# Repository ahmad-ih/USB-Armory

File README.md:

View this project on [CADLAB.io](https://cadlab.io/project/22758). 

# USB-Armory

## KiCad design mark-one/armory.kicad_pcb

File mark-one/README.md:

Introduction
============

USB armory | https://inversepath.com/usbarmory  
Copyright (c) F-Secure Corporation

The USB armory from [Inverse Path](https://inversepath.com) is an open source
hardware design, implementing a flash drive sized computer.

This repository is aimed towards developers, if you wish to purchase a USB
armory board please see the [ordering information](https://inversepath.com/usbarmory#ordering).

Revision information
====================

This directory contains the hardware design for the USB armory board, first
revision (Mark I).

Current schematics and layout files have been designed in KiCad (`release
2014-01-25 - 0.201403191418+4754~10~ubuntu12.04.1`)

PCB information
===============

6 layers, 2.00mm thickness  
Outer layers 0.5 oz base copper foil  
Inner layers   1 oz base copper foil  
width (X) 65.6 mm, height (Y) 19.5 mm  
Electroless Nickel Immersion Gold (ENIG) surface finish  
Selective hard gold (min 0.75um) plating for J2 (USB)  
Black resist, white component legend

Layers
------

Order and type of copper layers:  
  TOP:         signal, front components  
  SIGNAL 1:    signal  
  GND POWER 1: ground and power plane  
  GND POWER 2: ground and power plane  
  SIGNAL 2:    signal  
  BOTTOM:      signal, back components  

| Layer | Description               |  Thickness (in um)  |
|:-----:|---------------------------|:-------------------:|
|       | LPI mask                  |   15                |
|       | ENIG plating              |   18                |
|   1   | copper                    |   17                |
|       | prepreg, 3 x PP 1080      |  240 -> 220         |
|   2   | copper                    |   35                |
|       | core, FR4  35/35          |  300                |
|   3   | copper                    |   35                |
|       | prepreg, 4 x PP 7628      |  760 -> 720         |
|   4   | copper                    |   35                |
|       | core, FR4  35/35          |  300                |
|   5   | copper                    |   35                |
|       | prepreg, 3 x PP 1080      |  240 -> 220         |
|   6   | copper                    |   17                |
|       | ENIG plating              |   18                |
|       | LPI mask                  |   15                |

Material: Isola PCL370-HR
Total thickness: 2.0 mm

DRC information
---------------

Minimum track width:            0.127 mm  
Minimum via diameter:           0.406 mm  
Outer layer track width:        0.127 mm  
Outer layer isolation distance: 0.127 mm  
Outer layer annular ring:       0.075 mm  
Inner layer track width:        0.127 mm  
Inner layer isolation distance: 0.127 mm  
Inner layer annular ring:       0.075 mm  
Smallest final hole (plated):   0.150 mm

Regulatory compliance & handling
================================

The USB armory board is intended for use as a development platform for hardware
or software. The board is an open system design, which does not include a
shielded enclosure. This may cause interference to other electrical or
electronic devices in close proximity. In a domestic environment, this product
may cause radio interference in which case the user may be required to take
adequate measures. In addition, this board should not be used near any medical
equipment or RF devices.

The board is sensitive to ESD. Hold the board only by its edges. After removing
the board from its box, place it on a grounded, static-free surface.

The board can become hot, like any fan-less design, during continuous high CPU
loads, mind its temperature while handling it.

License
=======

USB armory | https://inversepath.com/usbarmory  
Copyright (c) F-Secure Corporation

This is an open hardware design licensed under the terms of the CERN Open
Hardware Licence (OHL) v1.2.

You may redistribute and modify this documentation under the terms of the CERN
OHL v.1.2 (http://ohwr.org/cernohl). This documentation is distributed WITHOUT
ANY EXPRESS OR IMPLIED WARRANTY, INCLUDING OF MERCHANTABILITY, SATISFACTORY
QUALITY AND FITNESS FOR A PARTICULAR PURPOSE. Please see the CERN OHL v.1.2 for
applicable conditions.

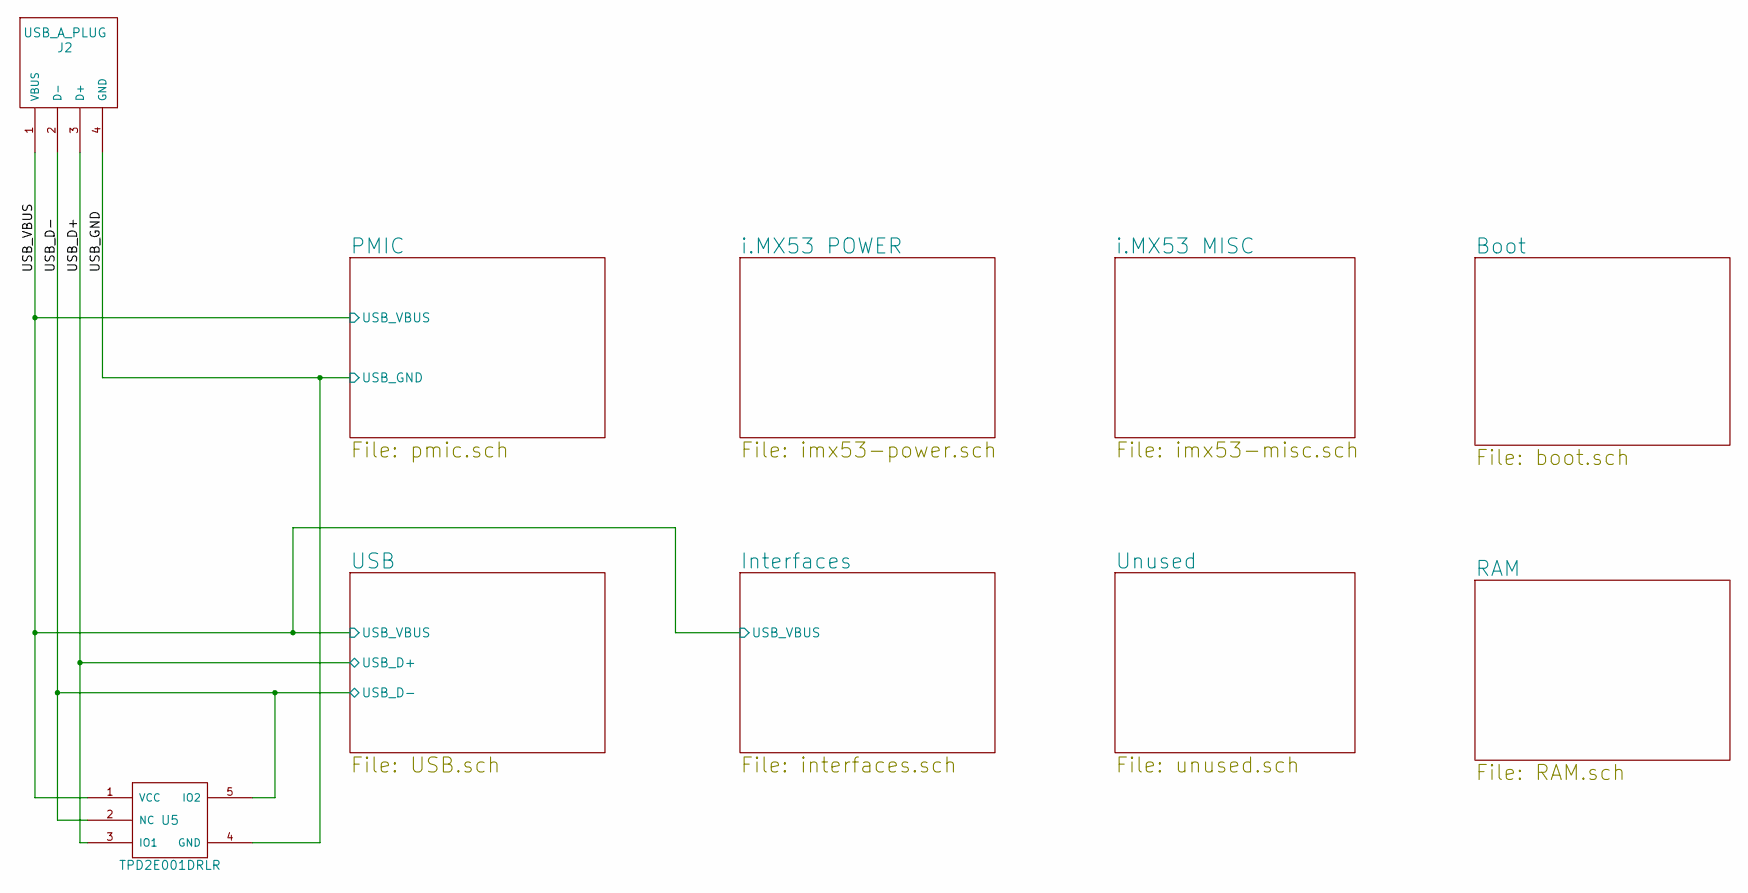
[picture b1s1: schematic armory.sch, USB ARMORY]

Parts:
J2: USB_A_PLUG; usb-PCB
U5: TPD2E001DRLR; R-PDSO-N5; Mfg PN TPD2E001DRLR

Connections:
/Interfaces/USB_VBUS: J2.1 (VBUS), U5.1 (VCC); also elsewhere on the board
/USB/USB_D+: J2.3 (D+), U5.3 (IO1); also elsewhere on the board
/USB/USB_D-: J2.2 (D-), U5.2 (NC), U5.5 (IO2); also elsewhere on the board
GND: J2.4 (GND), U5.4 (GND); also elsewhere on the board

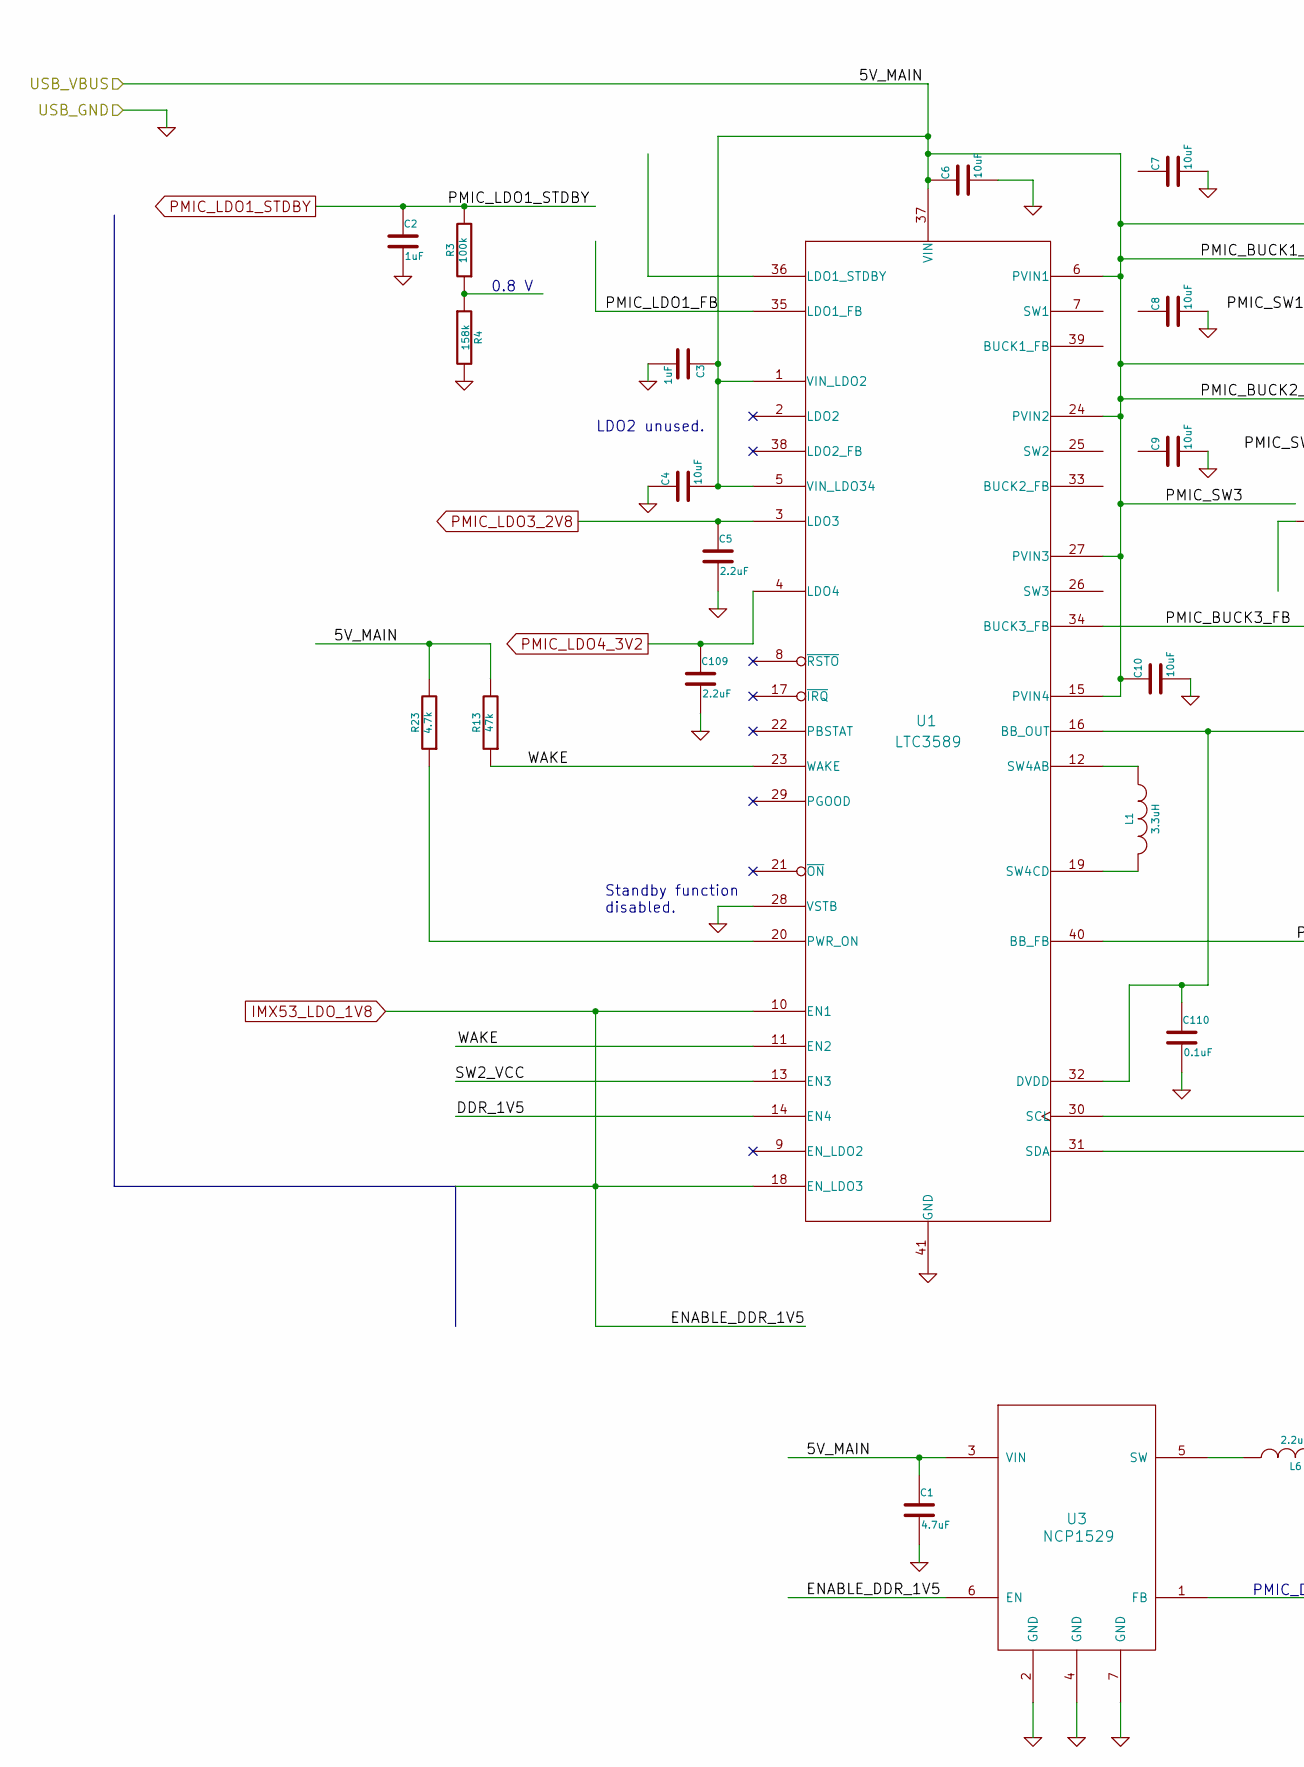
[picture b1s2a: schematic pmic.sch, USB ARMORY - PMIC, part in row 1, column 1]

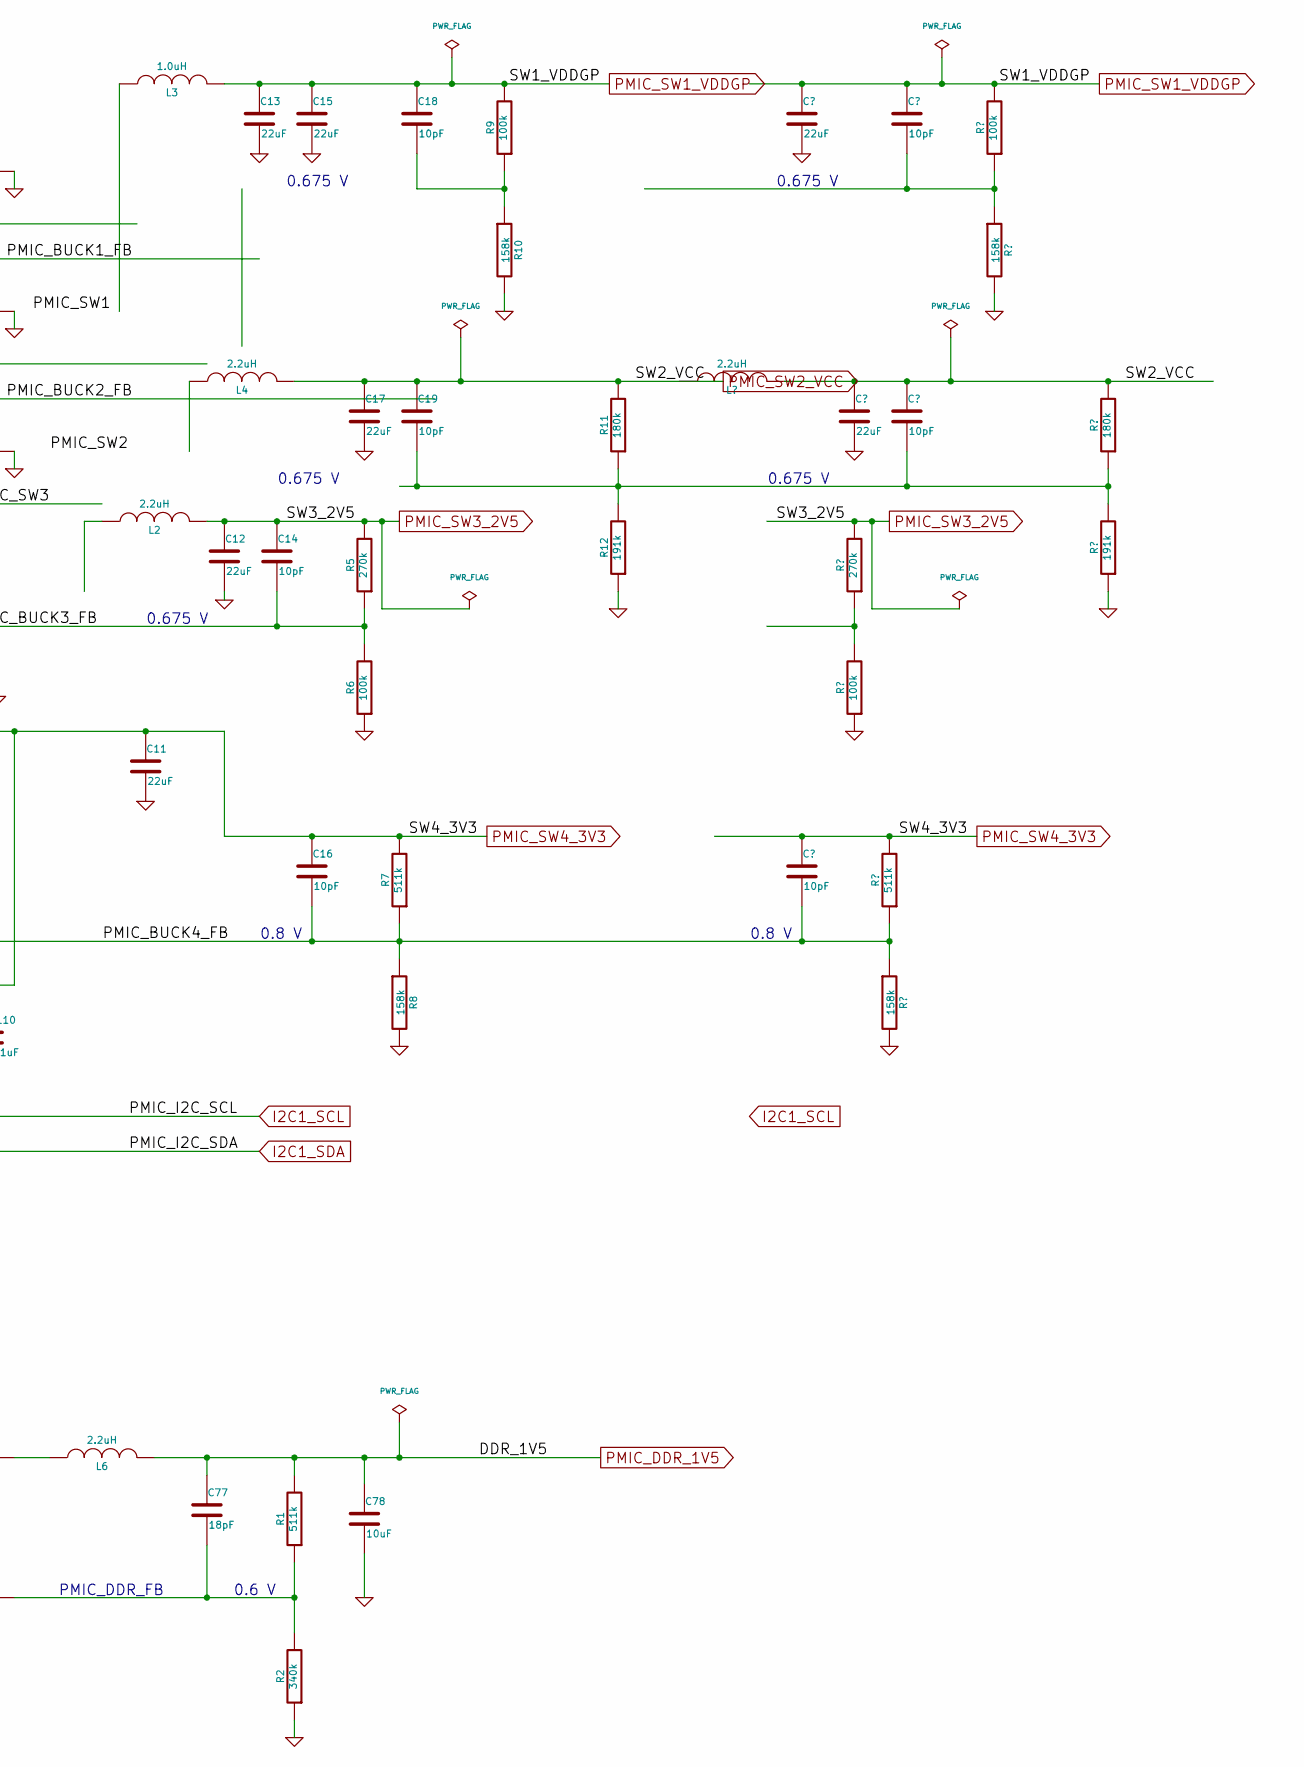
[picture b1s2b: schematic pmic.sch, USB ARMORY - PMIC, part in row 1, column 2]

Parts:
C1: 4.7uF; SM0603; Mfg PN CGB3B1X5R1A475K055AC
C2, C3: 1uF; SM0201; Mfg PN C0603X5R0J105M030BC
C4, C6, C7, C8, C9, C10, C78: 10uF; SM0603; Mfg PN C1608X5R1A106K080AC
C5, C109: 2.2uF; SM0402; Mfg PN C1005X5R0J225K050BC
C11, C12, C13, C15, C17: 22uF; SM0603; Mfg PN C1608X5R0J226M080AC
C14, C16, C18, C19: 10pF; SM0402; Mfg PN 04025U100JAT2A
C77: 18pF; SM0201; Mfg PN C0603C0G1H180J030BA
C110: 0.1uF; SM0201; Mfg PN C0603X5R0J104K030BC
L1: 3.3uH; VLS252012ET; Mfg PN VLS252012ET-3R3M
L2, L4, L6: 2.2uH; VLS252012ET; Mfg PN VLS252012ET-2R2M
L3: 1.0uH; VLS252012ET; Mfg PN VLS252012ET-1R0N
R1, R7: 511k; SM0201; Mfg PN CRCW0201511KFNED
R2: 340k; SM0201; Mfg PN CRCW0201340KFNED
R3, R6, R9: 100k; SM0201; Mfg PN CRCW0201100KFNED
R4, R8, R10: 158k; SM0201; Mfg PN CRCW0201158KFNED
R5: 270k; SM0201; Mfg PN CRCW0201270KFNED
R11: 180k; SM0201; Mfg PN CRCW0201180KFNED
R12: 191k; SM0201; Mfg PN CRCW0201191KFNED
R13: 47k; SM0201; Mfg PN CRCW020147K0FNED
R23: 4.7k; SM0201; Mfg PN CRCW02014K70FNED
U1: LTC3589; ltc3589-QFN40; Mfg PN LTC3589EUJ-2#PBF
U3: NCP1529; Mfg PN NCP1529MUTBG

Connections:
/Interfaces/USB_VBUS: C1.1, C3.1, C4.2, C6.1, C7.1, C8.1, C9.1, C10.1, R13.2, R23.2, U1.1 (VIN_LDO2), U1.5 (VIN_LDO34), U1.6 (PVIN1), U1.15 (PVIN4), U1.24 (PVIN2), U1.27 (PVIN3), U1.37 (VIN), U3.3 (VIN); also elsewhere on the board
/PMIC/PMIC_BUCK1_FB: C18.2, R9.1, R10.1
/PMIC/PMIC_BUCK2_FB: C19.2, R11.1, R12.2
/PMIC/PMIC_BUCK3_FB: C14.2, R5.1, R6.2, U1.34 (BUCK3_FB)
/PMIC/PMIC_BUCK4_FB: C16.2, R7.1, R8.1, U1.40 (BB_FB)
/PMIC/PMIC_LDO1_FB: R3.1, R4.1
/PMIC/PMIC_SW1: L3.1
/PMIC/PMIC_SW3: L2.1
GND: C1.2, C2.2, C3.2, C4.1, C5.2, C6.2, C7.2, C8.2, C9.2, C10.2, C11.2, C12.2, C13.2, C15.2, C17.2, C78.2, C109.2, C110.2, R2.1, R4.2, R6.1, R8.2, R10.2, R12.1, U1.28 (VSTB), U1.41 (GND), U3.2 (GND), U3.4 (GND), U3.7 (GND); also elsewhere on the board
IMX53_LDO_1V8: U1.10 (EN1), U1.18 (EN_LDO3), U3.6 (EN); also elsewhere on the board
unnamed: C77.2, R1.1, R2.2, U3.1 (FB)
unnamed: L1.1, U1.12 (SW4AB)
unnamed: L1.2, U1.19 (SW4CD)
unnamed: L6.1, U3.5 (SW)
unnamed: R13.1, U1.11 (EN2), U1.23 (WAKE)
unnamed: R23.1, U1.20 (PWR_ON)
PMIC_DDR_1V5: C77.1, C78.1, L6.2, R1.2, U1.14 (EN4); also elsewhere on the board
PMIC_LDO1_STDBY: C2.1, R3.2; also elsewhere on the board
PMIC_LDO3_2V8: C5.1, U1.3 (LDO3); also elsewhere on the board
PMIC_LDO4_3V2: C109.1, U1.4 (LDO4); also elsewhere on the board
PMIC_SW1_VDDGP: C13.1, C15.1, C18.1, L3.2, R9.2; also elsewhere on the board
PMIC_SW2_VCC: C17.1, C19.1, L4.2, R11.2, U1.13 (EN3); also elsewhere on the board
PMIC_SW3_2V5: C12.1, C14.1, L2.2, R5.2; also elsewhere on the board
PMIC_SW4_3V3: C11.1, C16.1, C110.1, R7.2, U1.16 (BB_OUT), U1.32 (DVDD); also elsewhere on the board

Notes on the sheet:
Standby function disabled.
0.8 V
0.675 V
LDO2 unused.
0.6 V
PMIC_DDR_FB

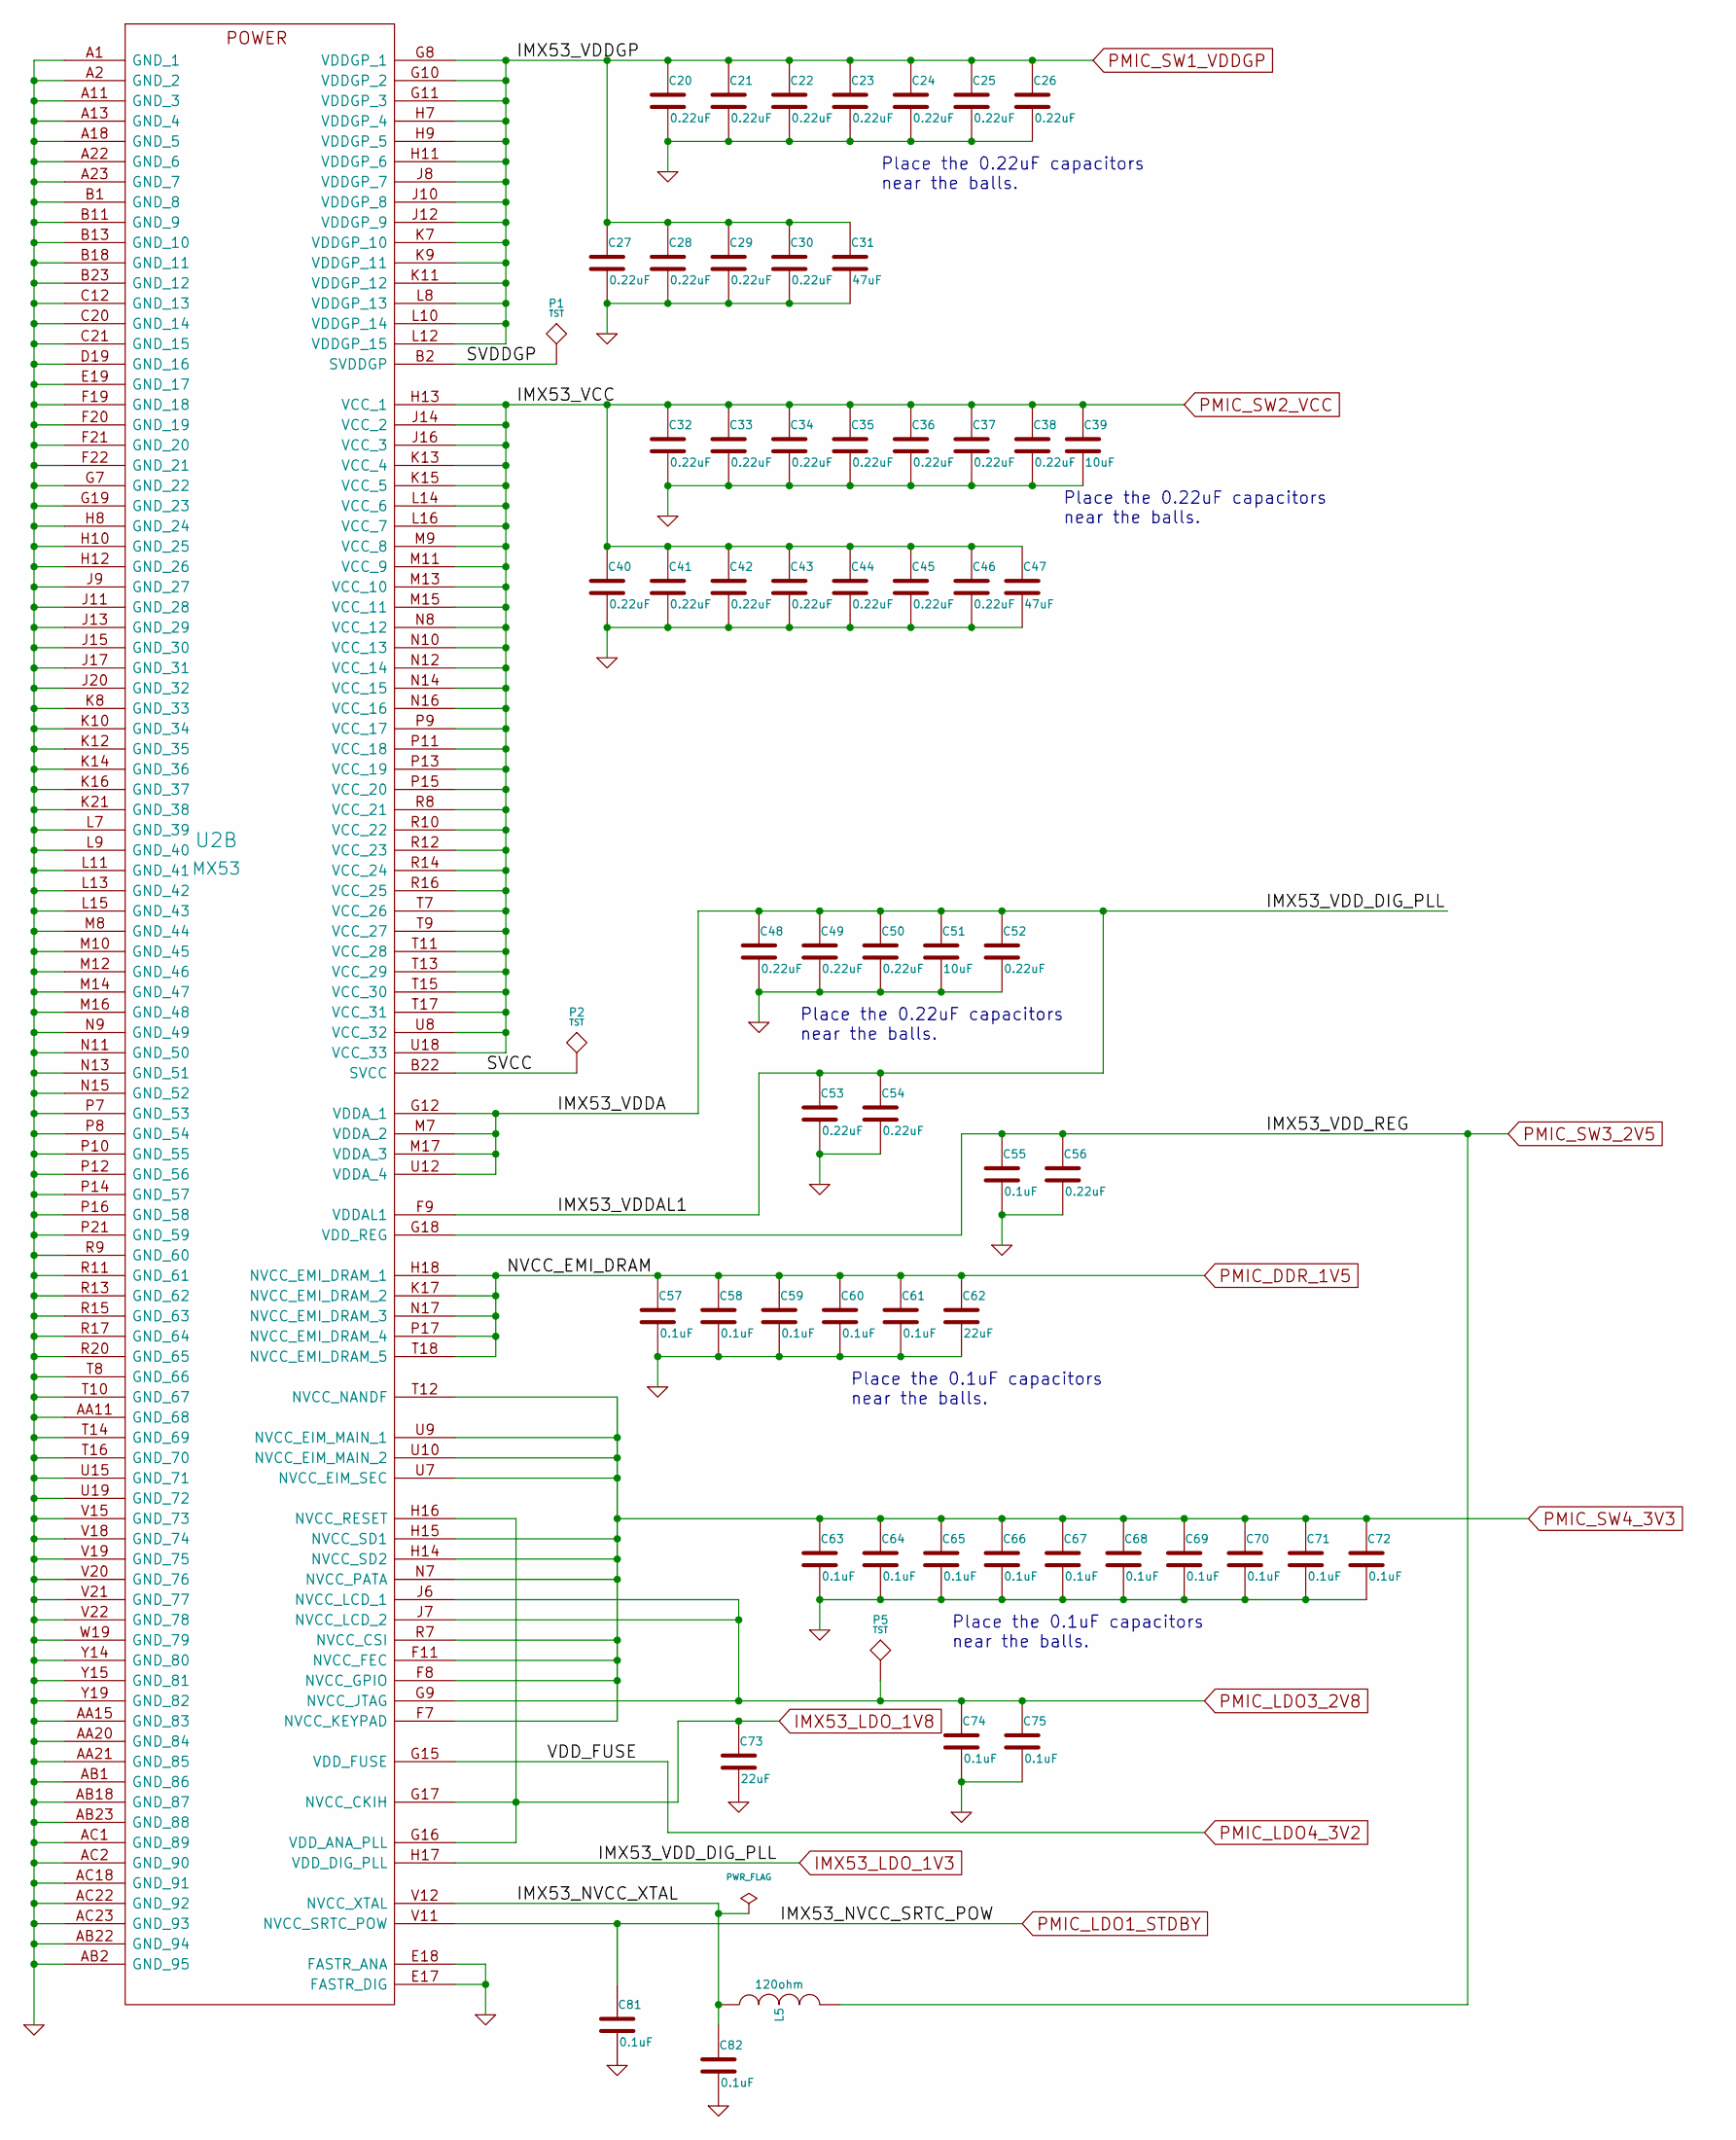
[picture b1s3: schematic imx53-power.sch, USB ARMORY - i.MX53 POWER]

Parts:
C20, C21, C22, C23, C24, C25, C26, C27, C28, C29, C30, C32, C33, C34, C35, C36, C37, C38, C40, C41, C42, C43, C44, C45, C46, C48, C49, C50, C52, C53, C54, C56: 0.22uF; SM0201; Mfg PN C0603X5R0J224M030BB
C31, C47: 47uF; SM0805; Mfg PN C2012X5R0J476M125AC
C39, C51: 10uF; SM0402; Mfg PN C1005X5R0J106M050BC
C55, C57, C58, C59, C60, C61, C63, C64, C65, C66, C67, C68, C69, C70, C71, C72, C74, C75, C81, C82: 0.1uF; SM0201; Mfg PN C0603X5R0J104K030BC
C62, C73: 22uF; SM0603; Mfg PN C1608X5R0J226M080AC
L5: 120ohm; SM0201; Mfg PN 742692003
P1, P2, P5: TST; TP
U2: MX53; Mfg PN MCIMX537CVV8C / MCIMX536AVV8C / MCIMX53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

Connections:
/i.MX53 POWER/IMX53_NVCC_XTAL: C82.1, L5.1, U2.V12 (NVCC_XTAL)
/i.MX53 POWER/SVCC: P2.1, U2.B22 (SVCC)
/i.MX53 POWER/SVDDGP: P1.1, U2.B2 (SVDDGP)
GND: C20.2, C21.2, C22.2, C23.2, C24.2, C25.2, C26.2, C27.2, C28.2, C29.2, C30.2, C31.2, C32.2, C33.2, C34.2, C35.2, C36.2, C37.2, C38.2, C39.2, C40.2, C41.2, C42.2, C43.2, C44.2, C45.2, C46.2, C47.2, C48.2, C49.2, C50.2, C51.2, C52.2, C53.2, C54.2, C55.2, C56.2, C57.2, C58.2, C59.2, C60.2, C61.2, C62.2, C63.2, C64.2, C65.2, C66.2, C67.2, C68.2, C69.2, C70.2, C71.2, C72.2, C73.2, C74.2, C75.2, C81.2, C82.2, U2.A1 (GND_1), U2.A2 (GND_2), U2.A11 (GND_3), U2.A13 (GND_4), U2.A18 (GND_5), U2.A22 (GND_6), U2.A23 (GND_7), U2.AA11 (GND_68), U2.AA15 (GND_83), U2.AA20 (GND_84), U2.AA21 (GND_85), U2.AB1 (GND_86), U2.AB2 (GND_95), U2.AB18 (GND_87), U2.AB22 (GND_94), U2.AB23 (GND_88), U2.AC1 (GND_89), U2.AC2 (GND_90), U2.AC18 (GND_91), U2.AC22 (GND_92), U2.AC23 (GND_93), U2.B1 (GND_8), U2.B11 (GND_9), U2.B13 (GND_10), U2.B18 (GND_11), U2.B23 (GND_12), U2.C12 (GND_13), U2.C20 (GND_14), U2.C21 (GND_15), U2.D19 (GND_16), U2.E17 (FASTR_DIG), U2.E18 (FASTR_ANA), U2.E19 (GND_17), U2.F19 (GND_18), U2.F20 (GND_19), U2.F21 (GND_20), U2.F22 (GND_21), U2.G7 (GND_22), U2.G19 (GND_23), U2.H8 (GND_24), U2.H10 (GND_25), U2.H12 (GND_26), U2.J9 (GND_27), U2.J11 (GND_28), U2.J13 (GND_29), U2.J15 (GND_30), U2.J17 (GND_31), U2.J20 (GND_32), U2.K8 (GND_33), U2.K10 (GND_34), U2.K12 (GND_35), U2.K14 (GND_36), U2.K16 (GND_37), U2.K21 (GND_38), U2.L7 (GND_39), U2.L9 (GND_40), U2.L11 (GND_41), U2.L13 (GND_42), U2.L15 (GND_43), U2.M8 (GND_44), U2.M10 (GND_45), U2.M12 (GND_46), U2.M14 (GND_47), U2.M16 (GND_48), U2.N9 (GND_49), U2.N11 (GND_50), U2.N13 (GND_51), U2.N15 (GND_52), U2.P7 (GND_53), U2.P8 (GND_54), U2.P10 (GND_55), U2.P12 (GND_56), U2.P14 (GND_57), U2.P16 (GND_58), U2.P21 (GND_59), U2.R9 (GND_60), U2.R11 (GND_61), U2.R13 (GND_62), U2.R15 (GND_63), U2.R17 (GND_64), U2.R20 (GND_65), U2.T8 (GND_66), U2.T10 (GND_67), U2.T14 (GND_69), U2.T16 (GND_70), U2.U15 (GND_71), U2.U19 (GND_72), U2.V15 (GND_73), U2.V18 (GND_74), U2.V19 (GND_75), U2.V20 (GND_76), U2.V21 (GND_77), U2.V22 (GND_78), U2.W19 (GND_79), U2.Y14 (GND_80), U2.Y15 (GND_81), U2.Y19 (GND_82); also elsewhere on the board
IMX53_LDO_1V3: C48.1, C49.1, C50.1, C51.1, C52.1, C53.1, C54.1, U2.F9 (VDDAL1), U2.G12 (VDDA_1), U2.H17 (VDD_DIG_PLL), U2.M7 (VDDA_2), U2.M17 (VDDA_3), U2.U12 (VDDA_4)
IMX53_LDO_1V8: C73.1, U2.G16 (VDD_ANA_PLL), U2.G17 (NVCC_CKIH), U2.H16 (NVCC_RESET); also elsewhere on the board
PMIC_DDR_1V5: C57.1, C58.1, C59.1, C60.1, C61.1, C62.1, U2.H18 (NVCC_EMI_DRAM_1), U2.K17 (NVCC_EMI_DRAM_2), U2.N17 (NVCC_EMI_DRAM_3), U2.P17 (NVCC_EMI_DRAM_4), U2.T18 (NVCC_EMI_DRAM_5); also elsewhere on the board
PMIC_LDO1_STDBY: C81.1, U2.V11 (NVCC_SRTC_POW); also elsewhere on the board
PMIC_LDO3_2V8: C74.1, C75.1, P5.1, U2.G9 (NVCC_JTAG), U2.J6 (NVCC_LCD_1), U2.J7 (NVCC_LCD_2); also elsewhere on the board
PMIC_LDO4_3V2: U2.G15 (VDD_FUSE); also elsewhere on the board
PMIC_SW1_VDDGP: C20.1, C21.1, C22.1, C23.1, C24.1, C25.1, C26.1, C27.1, C28.1, C29.1, C30.1, C31.1, U2.G8 (VDDGP_1), U2.G10 (VDDGP_2), U2.G11 (VDDGP_3), U2.H7 (VDDGP_4), U2.H9 (VDDGP_5), U2.H11 (VDDGP_6), U2.J8 (VDDGP_7), U2.J10 (VDDGP_8), U2.J12 (VDDGP_9), U2.K7 (VDDGP_10), U2.K9 (VDDGP_11), U2.K11 (VDDGP_12), U2.L8 (VDDGP_13), U2.L10 (VDDGP_14), U2.L12 (VDDGP_15); also elsewhere on the board
PMIC_SW2_VCC: C32.1, C33.1, C34.1, C35.1, C36.1, C37.1, C38.1, C39.1, C40.1, C41.1, C42.1, C43.1, C44.1, C45.1, C46.1, C47.1, U2.H13 (VCC_1), U2.J14 (VCC_2), U2.J16 (VCC_3), U2.K13 (VCC_4), U2.K15 (VCC_5), U2.L14 (VCC_6), U2.L16 (VCC_7), U2.M9 (VCC_8), U2.M11 (VCC_9), U2.M13 (VCC_10), U2.M15 (VCC_11), U2.N8 (VCC_12), U2.N10 (VCC_13), U2.N12 (VCC_14), U2.N14 (VCC_15), U2.N16 (VCC_16), U2.P9 (VCC_17), U2.P11 (VCC_18), U2.P13 (VCC_19), U2.P15 (VCC_20), U2.R8 (VCC_21), U2.R10 (VCC_22), U2.R12 (VCC_23), U2.R14 (VCC_24), U2.R16 (VCC_25), U2.T7 (VCC_26), U2.T9 (VCC_27), U2.T11 (VCC_28), U2.T13 (VCC_29), U2.T15 (VCC_30), U2.T17 (VCC_31), U2.U8 (VCC_32), U2.U18 (VCC_33); also elsewhere on the board
PMIC_SW3_2V5: C55.1, C56.1, L5.2, U2.G18 (VDD_REG); also elsewhere on the board
PMIC_SW4_3V3: C63.1, C64.1, C65.1, C66.1, C67.1, C68.1, C69.1, C70.1, C71.1, C72.1, U2.F7 (NVCC_KEYPAD), U2.F8 (NVCC_GPIO), U2.F11 (NVCC_FEC), U2.H14 (NVCC_SD2), U2.H15 (NVCC_SD1), U2.N7 (NVCC_PATA), U2.R7 (NVCC_CSI), U2.T12 (NVCC_NANDF), U2.U7 (NVCC_EIM_SEC), U2.U9 (NVCC_EIM_MAIN_1), U2.U10 (NVCC_EIM_MAIN_2); also elsewhere on the board

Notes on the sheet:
Place the 0.22uF capacitors near the balls.
Place the 0.1uF capacitors near the balls.

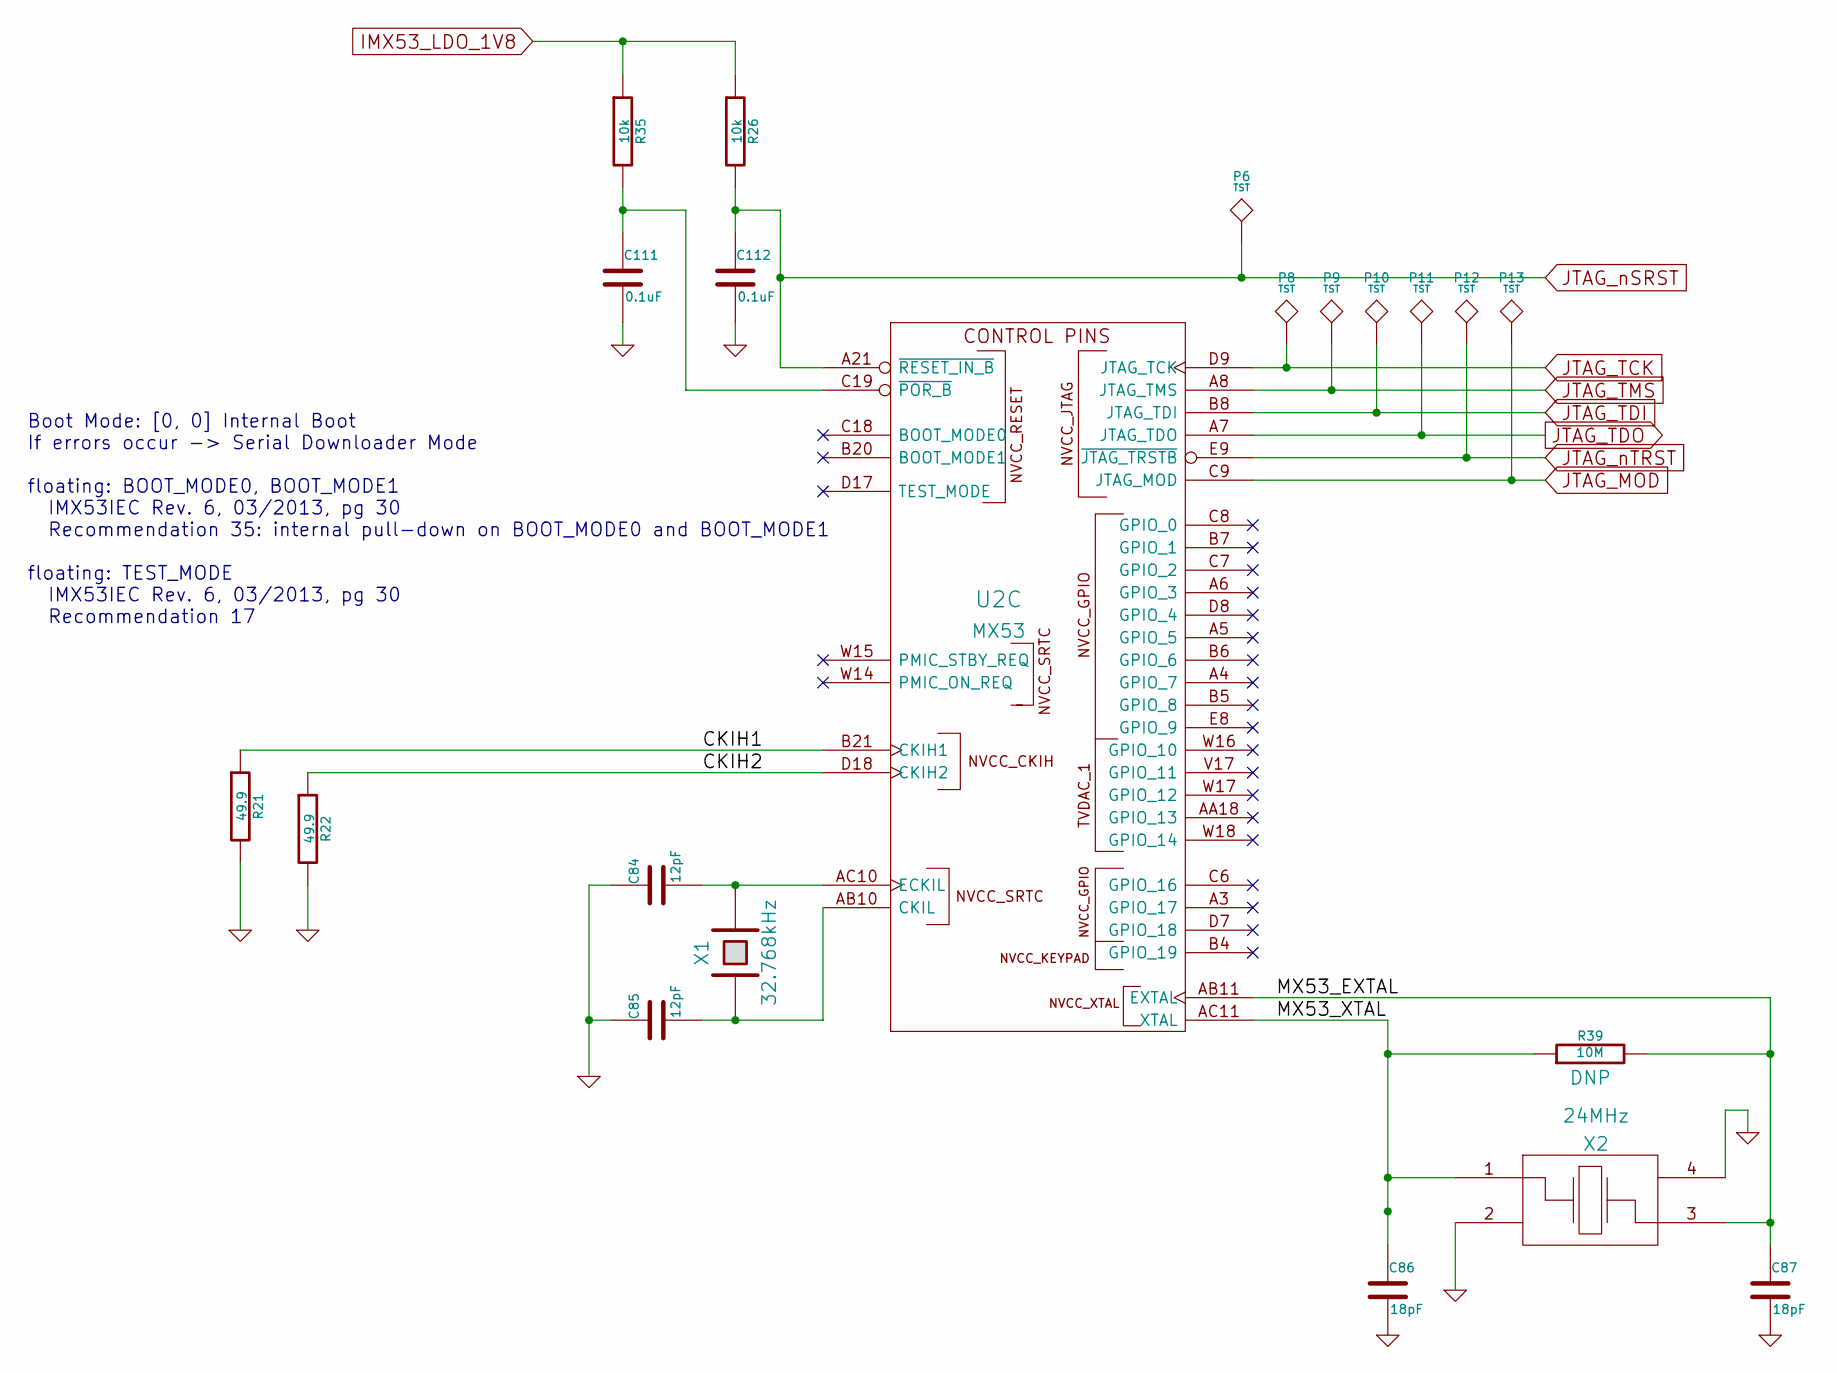
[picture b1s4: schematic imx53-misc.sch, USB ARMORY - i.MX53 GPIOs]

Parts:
C84, C85: 12pF; SM0201; Mfg PN C0603C0G1E120J030BA
C86, C87: 18pF; SM0201; Mfg PN C0603C0G1H180J030BA
C111, C112: 0.1uF; SM0201; Mfg PN C0603X5R0J104K030BC
P6, P8, P9, P10, P11, P12, P13: TST; TP
R21, R22: 49.9; SM0201; Mfg PN CRCW020149R9FNED
R26, R35: 10k; SM0201; Mfg PN CRCW020110K0FNED
R39: 10M; SM0201; Mfg PN CRCW020110M0FNED
U2: MX53
X1: 32.768kHz; CRYSTAL-32k-B; Mfg PN ABS07-32.768KHZ-9-T
X2: 24MHz; CRYSTAL-24M-B; Mfg PN 7M-24.000MEEQ-T

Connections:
/i.MX53 MISC/CKIH1: R21.1, U2.B21 (CKIH1)
/i.MX53 MISC/CKIH2: R22.1, U2.D18 (CKIH2)
/i.MX53 MISC/MX53_EXTAL: C87.1, R39.2, U2.AB11 (EXTAL), X2.3
/i.MX53 MISC/MX53_XTAL: C86.1, R39.1, U2.AC11 (XTAL), X2.1
GND: C84.1, C85.1, C86.2, C87.2, C111.2, C112.2, R21.2, R22.2, X2.2, X2.4; also elsewhere on the board
IMX53_LDO_1V8: R26.1, R35.1; also elsewhere on the board
JTAG_MOD: P13.1, U2.C9 (JTAG_MOD)
JTAG_TCK: P8.1, U2.D9 (JTAG_TCK)
JTAG_TDI: P10.1, U2.B8 (JTAG_TDI)
JTAG_TDO: P11.1, U2.A7 (JTAG_TDO)
JTAG_TMS: P9.1, U2.A8 (JTAG_TMS)
JTAG_nSRST: C112.1, P6.1, R26.2, U2.A21 (~RESET_IN_B)
JTAG_nTRST: P12.1, U2.E9 (~JTAG_TRSTB)
unnamed: C84.2, U2.AC10 (ECKIL), X1.2
unnamed: C85.2, U2.AB10 (CKIL), X1.1
unnamed: C111.1, R35.2, U2.C19 (~POR_B)

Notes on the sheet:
Boot Mode: [0, 0] Internal Boot If errors occur -> Serial Downloader Mode floating: BOOT_MODE0, BOOT_MODE1 IMX53IEC Rev. 6, 03/2013, pg 30 Recommendation 35: internal pull-down on BOOT_MODE0 and BOOT_MODE1 floating: TEST_MODE IMX53IEC Rev. 6, 03/2013, pg 30 Recommendation 17

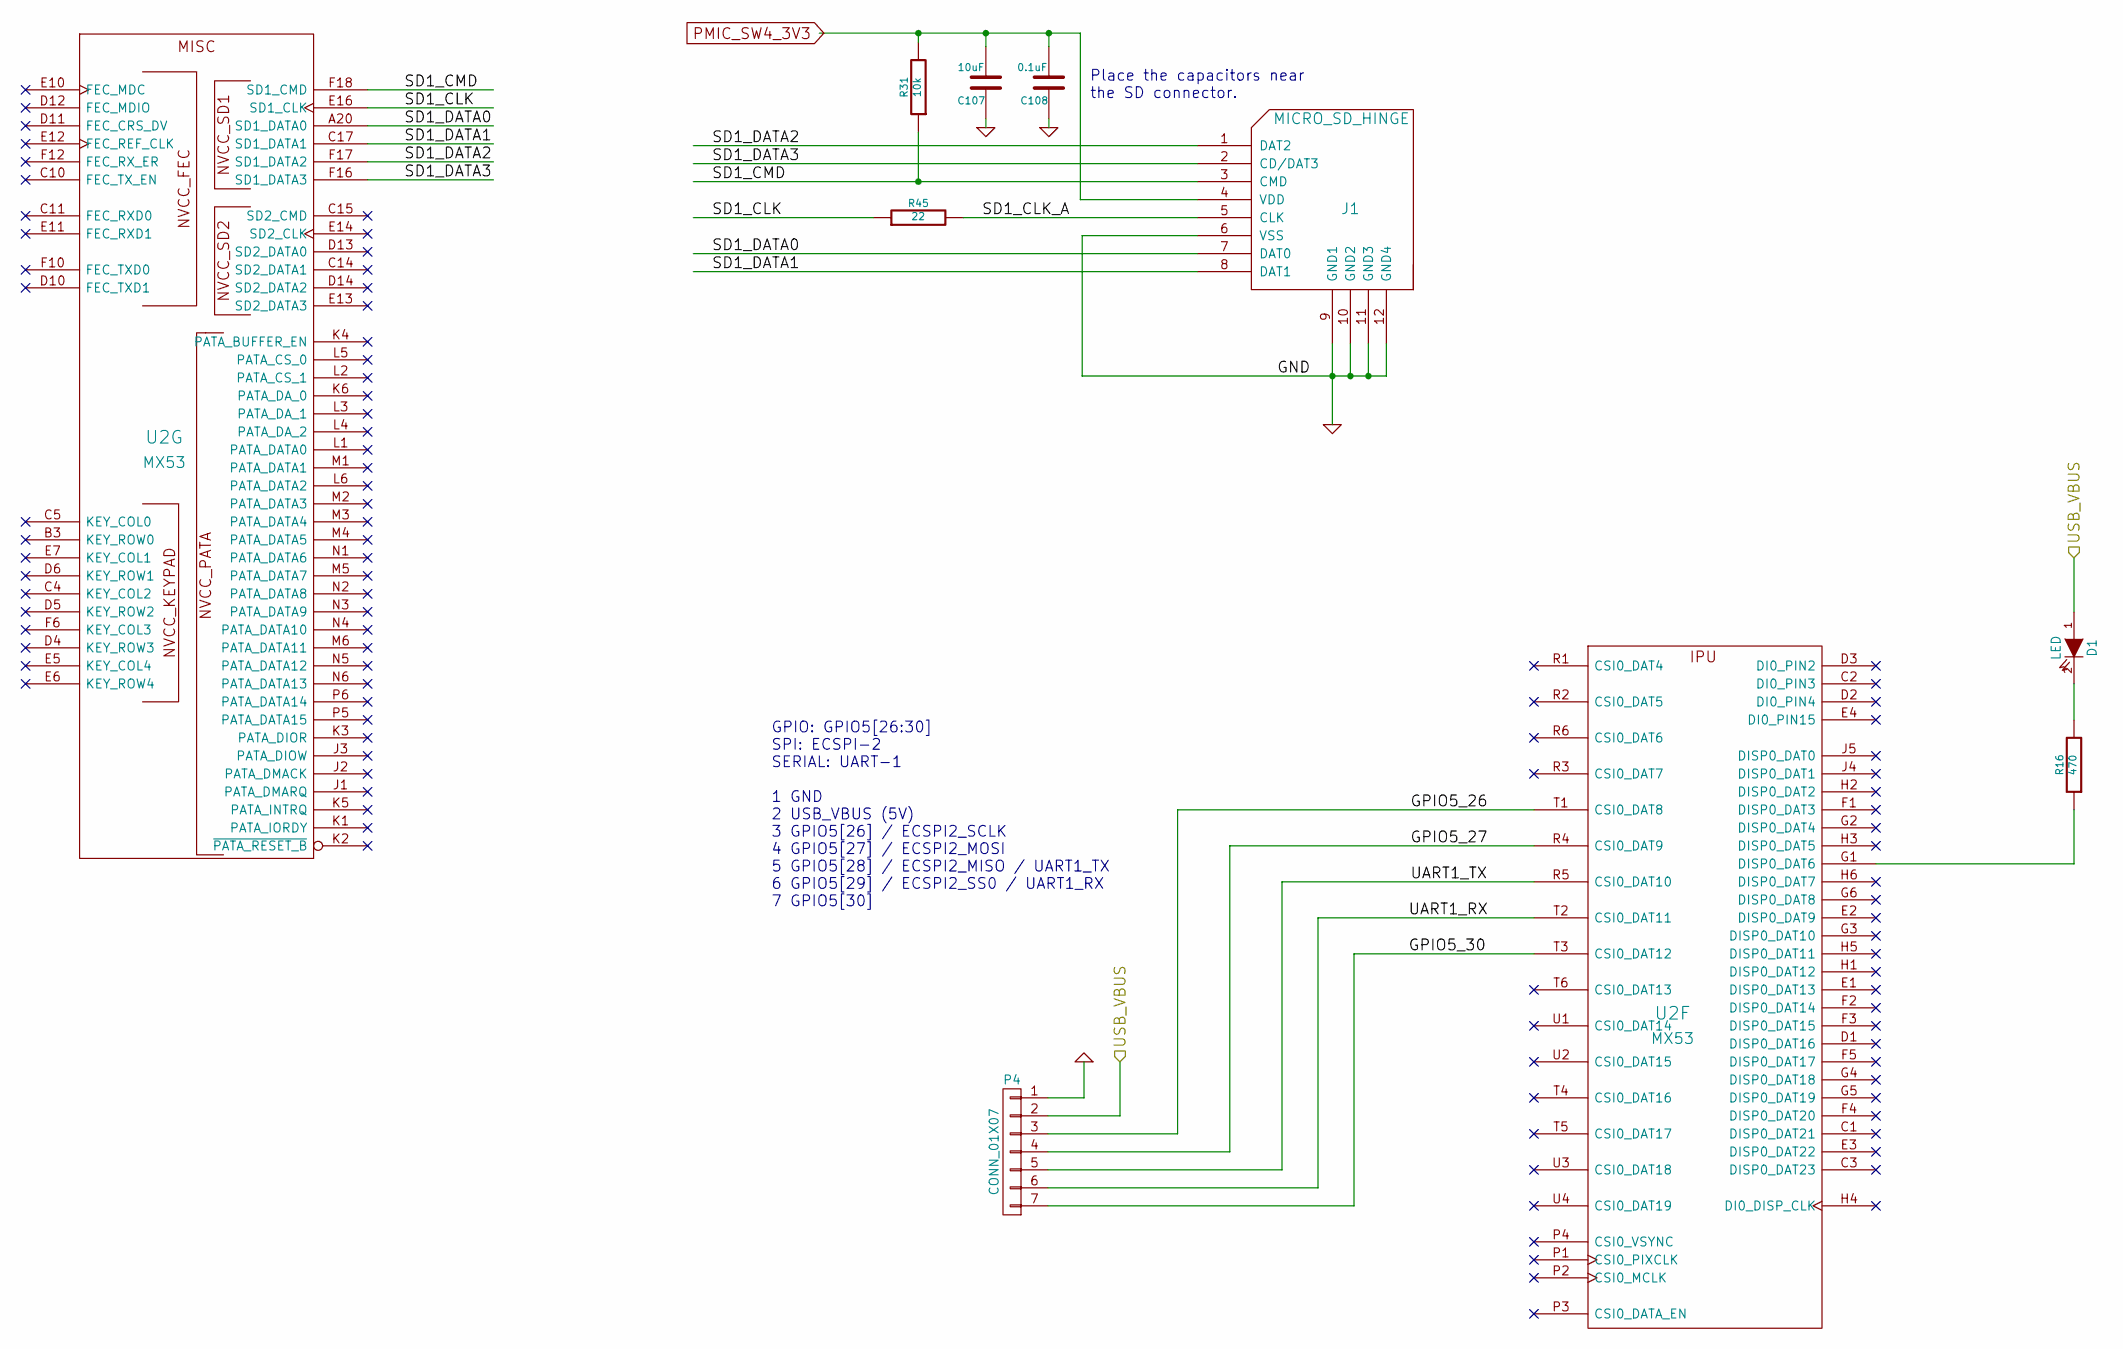
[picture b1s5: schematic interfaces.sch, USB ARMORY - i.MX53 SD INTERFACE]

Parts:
C107: 10uF; SM0603; Mfg PN C1608X5R1A106K080AC
C108: 0.1uF; SM0201; Mfg PN C0603X5R0J104K030BC
D1: LED; SM0603LED; Mfg PN VLMW1300-GS08
J1: MICRO_SD_HINGE; MICRO_SD_HINGE_AMP; Mfg PN 101-00303-68
P4: CONN_01X07; pinhead-1X7
R16: 470; SM0201; Mfg PN CRCW0201470RFNED
R31: 10k; SM0201; Mfg PN CRCW020110K0FNED
R45: 22; SM0201; Mfg PN CRCW020122R0FNED
U2: MX53

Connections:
/Interfaces/GPIO5_26: P4.3, U2.T1 (CSI0_DAT8); also elsewhere on the board
/Interfaces/GPIO5_27: P4.4, U2.R4 (CSI0_DAT9); also elsewhere on the board
/Interfaces/GPIO5_30: P4.7, U2.T3 (CSI0_DAT12); also elsewhere on the board
/Interfaces/SD1_CLK: R45.1, U2.E16 (SD1_CLK)
/Interfaces/SD1_CLK_A: J1.5 (CLK), R45.2
/Interfaces/SD1_CMD: J1.3 (CMD), R31.1, U2.F18 (SD1_CMD)
/Interfaces/SD1_DATA0: J1.7 (DAT0), U2.A20 (SD1_DATA0)
/Interfaces/SD1_DATA1: J1.8 (DAT1), U2.C17 (SD1_DATA1)
/Interfaces/SD1_DATA2: J1.1 (DAT2), U2.F17 (SD1_DATA2)
/Interfaces/SD1_DATA3: J1.2 (CD/DAT3), U2.F16 (SD1_DATA3)
/Interfaces/UART1_RX: P4.6, U2.T2 (CSI0_DAT11); also elsewhere on the board
/Interfaces/UART1_TX: P4.5, U2.R5 (CSI0_DAT10); also elsewhere on the board
/Interfaces/USB_VBUS: D1.1 (A), P4.2; also elsewhere on the board
GND: C107.1, C108.1, J1.6 (VSS), J1.9 (GND1), J1.10 (GND2), J1.11 (GND3), J1.12 (GND4), P4.1; also elsewhere on the board
unnamed: D1.2 (K), R16.2
unnamed: R16.1, U2.G1 (DISP0_DAT6)
PMIC_SW4_3V3: C107.2, C108.2, J1.4 (VDD), R31.2; also elsewhere on the board

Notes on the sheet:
Place the capacitors near the SD connector.
GPIO: GPIO5[26:30] SPI: ECSPI-2 SERIAL: UART-1 1 GND 2 USB_VBUS (5V) 3 GPIO5[26] / ECSPI2_SCLK 4 GPIO5[27] / ECSPI2_MOSI 5 GPIO5[28] / ECSPI2_MISO / UART1_TX 6 GPIO5[29] / ECSPI2_SS0 / UART1_RX 7 GPIO5[30]

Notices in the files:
mark-one/RAM.sch:
Copyright © F-Secure Corporation
License: CERN OHL v1.2
